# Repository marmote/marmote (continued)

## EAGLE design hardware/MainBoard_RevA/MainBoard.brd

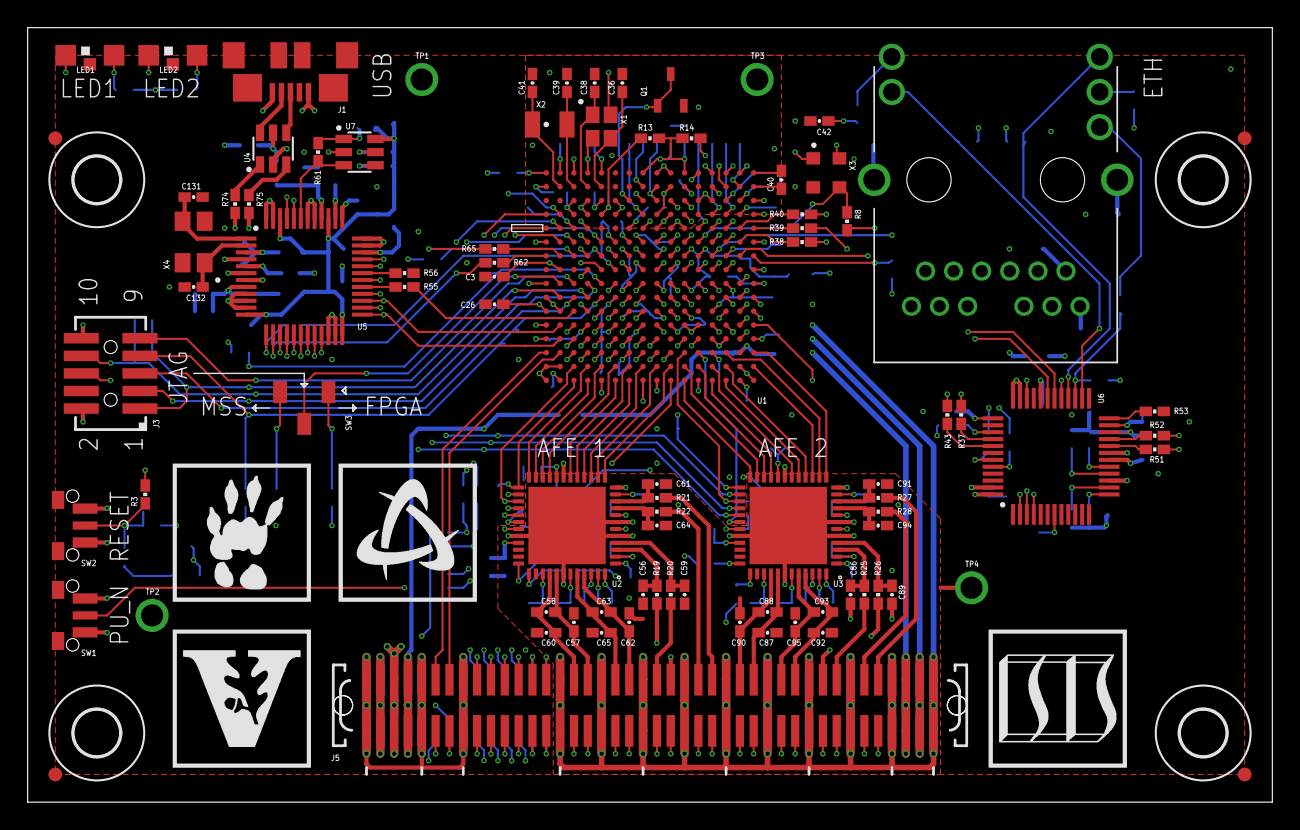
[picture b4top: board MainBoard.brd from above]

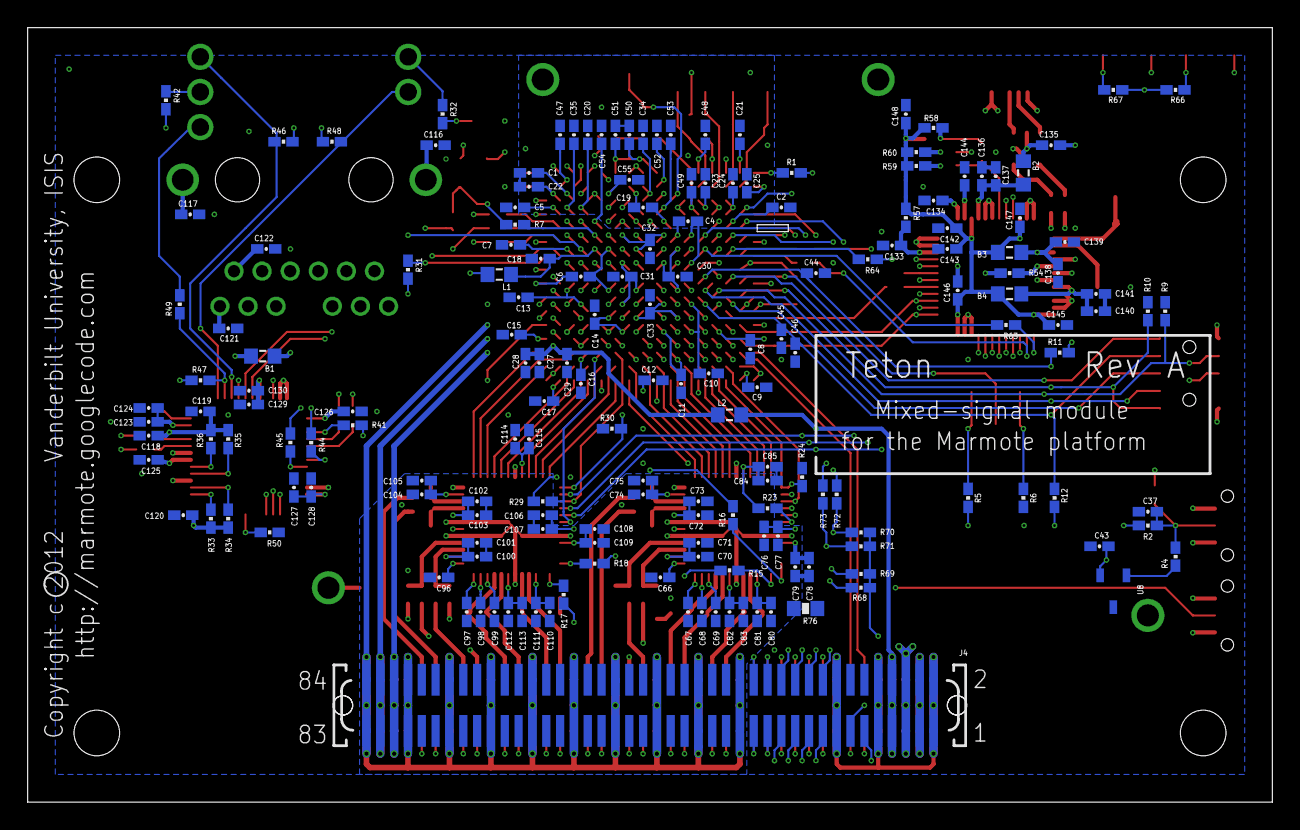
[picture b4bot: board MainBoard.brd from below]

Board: 6 copper layers, 90.0 x 56.0 mm, 269 parts (175 on the bottom side), 224 nets.

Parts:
B1: 70R/4A; L0603
B2, B3, B4: 600R/0.5A; L0603
C1, C40, C70, C72, C74, C76, C78, C80, C82, C84, C100, C102, C104, C106, C108, C110, C112, C114: 2.2uF; C0402
C2, C3, C4, C5, C6, C7, C8, C9, C10, C11, C12, C13, C14, C15, C16, C17, C18, C19, C20, C21, C22, C23, C24, C25, C26, C28, C30, C31, C32, C33, C34, C35, C37, C43, C44, C69, C71, C73, C75, C77, C79, C81, C83, C85, C99, C101, C103, C105, C107, C109, C111, C113, C115, C118, C119, C120, C121, C122, C124, C125, C126, C128, C130, C134, C137, C139, C141, C143, C144, C145, C146, C147, C148: 0.1uF; C0402
C27, C49, C50, C51, C123, C127, C129, C136, C138, C140, C142: 4.7uF; C0402
C29, C42, C46: 0.01uF; C0402
C36, C38, C131, C132: 10pF; C0402
C39, C41: 4pF; C0402
C45, C66, C67, C68, C96, C97, C98: 0.33uF; C0402
C47, C48, C52, C53, C54, C55, C57, C58, C60, C62, C63, C65, C87, C88, C90, C92, C93, C95: C0402
C56, C59, C61, C64, C86, C89, C91, C94: 22pF; C0402
C116, C117: 1000pF; C0402
C133, C135: 10nF; C0402
J1: CON-ZX62R-B-5P; ZX62R-B-5P
J2: CON-RJ45-J0G-0007NL; J0G-0007NL
J3: CON-FTSH-105-01-L-DV-K; FTSH-105-01-L-DV-K
J4: CON-71741-2184-BOT; 71742-3003-BOT
J5: CON-71741-2184-TOP; 71741-0002
L1, L2: 33nH; L0603
LED1, LED2: LED1208-RA
LOGO1: LOGO-VANDERBILT-600MIL-10MM-SS; LOGO-VANDERBILT-10MM-SILKSCREEN
LOGO2: LOGO-ISIS-600MIL-10MM-SS; LOGO-ISIS-10MM-SILKSCREEN
LOGO3: LOGO-MARMOTE-600MIL-10MM-SS; LOGO-MARMOTE-10MM-SILKSCREEN
LOGO4: LOGO-SMARTFUSION-600MIL-10MM-SS; LOGO-SMARTFUSION-10MM-SILKSCREEN
M1, M2, M3, M4: MOUNT-HOLE3.3; 3,3
M5, M6, M7, M8: FIDUCIAL1X2; FIDUCIAL-1X2
Q1: MMBT3904; SOT23-3L
R1, R2, R57, R58, R59, R60: 10k; R0402
R3, R7, R8, R62, R63, R64, R65: 39; R0402
R4, R11, R12, R13, R14, R15, R16, R17, R18, R49, R74, R75: 0; R0402
R5, R6, R9, R10: 1k; R0402
R19, R20, R21, R22, R25, R26, R27, R28: 24.9; R0402
R23, R24, R29, R30, R68, R69: 100k; R0402
R31: 1.5k; R0402
R32, R42, R66, R72, R73: 100; R0402
R33, R34, R35, R36: 49.9; R0402
R37, R38, R39, R40, R43, R44, R45: 22; R0402
R41, R46, R47, R48, R50, R51, R52: 2.2k; R0402
R53: 4.87k; R0402
R54: 12k; R0402
R55: 27; R0402
R56: 39k; R0402
R61: 2k; R0402
R67: 330; R0402
R70, R71: 4.7k; R0402
R76: 0; R0603
SW1, SW2: SWITCH-ESWITCH-TL3340G; TL3340
SW3: SWITCH-CJS-1200TA; SWITCH-DIP-CJS
TP1, TP2: TESTPOINT-YELLOW; TESTPOINT
TP3, TP4: TESTPOINT-GREEN; TESTPOINT
U1: A2F500M3G-1FGG256; FG256
U2, U3: MAX19706-T4877-4; TQFN-48
U4: USBLC6-2SC6; SOT23-6L
U5: FT232HL; LQFP-48
U6: DP83848C-VBH48A; LQFP-48
U7: 93LC56BT-OT; SOT23-6L
U8: DS1818-10-SOT-23; SOT23-3L
X1: ECX-2236-200; ECX-2236
X2: ECX-31B
X3: ASEM1-C; ASEM1
X4: ECX-42-120; ECX-42

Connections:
!AFE1_SHDN: R24.2, U1.A14, U2.25
!AFE2_SHDN: R30.2, U1.D6, U3.25
!MSS_RESET: R3.2, U1.K4, U6.29
!MSS_RESET_PB: C37.1, R2.1, R3.1, R4.2, SW2.2
!OE: U1.E16, U5.30
!PWRSAV: R56.1, U5.31
!RD: U1.D14, U5.26
!RXF: U1.D13, U5.21
!SIWU: U1.E14, U5.28
!SPI1_SS_AFE1: R23.1, U1.C14, U2.30
!SPI1_SS_AFE2: R29.1, U1.C5, U3.30
!TXE: U1.D15, U5.25
!USB_RESET: C133.1, R57.2, U5.34
!WAKEUP: J4.27, J5.27, R1.2, SW1.2, U1.T16
!WR: U1.E15, U5.27
A1V5: C34.1, C35.1, J4.79, J4.80, J5.79, J5.80, U1.N3, U1.P8, U1.R8
A3V3: C19.1, C20.1, C21.1, C22.1, C23.1, C24.1, C25.1, C69.1, C70.1, C71.1, C72.1, C73.1, C74.1, C75.1, C76.1, C77.1, C78.1, C79.1, C80.1, C81.1, C82.1, C83.1, C99.1, C100.1, C101.1, C102.1, C103.1, C104.1, C105.1, C106.1, C107.1, C108.1, C109.1, C110.1, C111.1, C112.1, C113.1, J4.81, J4.82, J5.81, J5.82, R14.2, U1.N4, U1.N8, U1.N14, U1.P2, U1.P12, U1.P14, U1.R7, U1.R16, U1.T15, U2.2, U2.8, U2.11, U2.31, U2.33, U2.39, U2.43, U2.46, U3.2, U3.8, U3.11, U3.31, U3.33, U3.39, U3.43, U3.46
ACBUS8: U1.E12, U5.32
ACBUS9: U1.F12, U5.33
ADC1+: J5.46, R19.2
ADC1-: J5.44, R20.2
ADC1-IAN: C59.2, R20.1, U2.4
ADC1-IAP: C56.1, R19.1, U2.3
ADC2+: J5.52, R21.2
ADC2-: J5.50, R22.2
ADC2-QAN: C64.2, R22.1, U2.9
ADC2-QAP: C61.1, R21.1, U2.10
ADC3+: J5.70, R25.2
ADC3-: J5.68, R26.2
ADC3-IAN: C89.2, R26.1, U3.4
ADC3-IAP: C86.1, R25.1, U3.3
ADC4+: J5.76, R27.2
ADC4-: J5.74, R28.2
ADC4-QAN: C94.2, R28.1, U3.9
ADC4-QAP: C91.1, R27.1, U3.10
AFE1_CLK: U1.A7, U2.6
AFE1_COM: C68.1, U2.47
AFE1_DB0: U1.B7, U2.13
AFE1_DB1: U1.B8, U2.14
AFE1_DB2: U1.B9, U2.15
AFE1_DB3: U1.A10, U2.16
AFE1_DB4: U1.B10, U2.17
AFE1_DB5: U1.A11, U2.18
AFE1_DB6: U1.B11, U2.21
AFE1_DB7: U1.B12, U2.22
AFE1_DB8: U1.A13, U2.23
AFE1_DB9: U1.B13, U2.24
AFE1_REFN: C67.1, U2.48
AFE1_REFP: C66.1, U2.1
AFE1_T/!R: U1.B14, U2.27
AFE2_CLK: U1.E1, U3.6
AFE2_COM: C98.1, U3.47
AFE2_DB0: U1.C1, U3.13
AFE2_DB1: U1.C3, U3.14
AFE2_DB2: U1.B1, U3.15
AFE2_DB3: U1.B3, U3.16
AFE2_DB4: U1.A3, U3.17
AFE2_DB5: U1.B4, U3.18
AFE2_DB6: U1.A4, U3.21
AFE2_DB7: U1.B5, U3.22
AFE2_DB8: U1.B6, U3.23
AFE2_DB9: U1.A6, U3.24
AFE2_REFN: C97.1, U3.48
AFE2_REFP: C96.1, U3.1
AFE2_T/!R: U1.C6, U3.27
AGND: C1.2, C19.2, C20.2, C21.2, C22.2, C23.2, C24.2, C25.2, C34.2, C35.2, C36.2, C38.2, C39.2, C41.2, C47.2, C48.2, C49.2, C50.2, C51.2, C52.2, C53.2, C54.2, C55.2, C56.2, C57.2, C59.1, C60.1, C61.2, C62.2, C64.1, C65.1, C66.2, C67.2, C68.2, C69.2, C70.2, C71.2, C72.2, C73.2, C74.2, C75.2, C76.2, C77.2, C78.2, C79.2, C80.2, C81.2, C82.2, C83.2, C86.2, C87.2, C89.1, C90.1, C91.2, C92.2, C94.1, C95.1, C96.2, C97.2, C98.2, C99.2, C100.2, C101.2, C102.2, C103.2, C104.2, C105.2, C106.2, C107.2, C108.2, C109.2, C110.2, C111.2, C112.2, C113.2, J4.29, J4.30, J4.35, J4.36, J4.41, J4.42, J4.47, J4.48, J4.53, J4.54, J4.59, J4.60, J4.65, J4.66, J4.71, J4.72, J4.77, J4.78, J4.83, J4.84, J5.29, J5.30, J5.35, J5.36, J5.41, J5.42, J5.47, J5.48, J5.53, J5.54, J5.59, J5.60, J5.65, J5.66, J5.71, J5.72, J5.77, J5.78, J5.83, J5.84, Q1.2, R76.2, TP3.1, TP4.1, U1.D2, U1.J4, U1.M6, U1.M7, U1.M8, U1.M10, U1.N7, U1.N11, U1.N13, U1.P1, U1.P4, U1.P5, U1.P11, U1.P13, U1.T4, U1.T7, U1.T8, U1.T13, U1.T14, U2.5, U2.7, U2.12, U2.32, U2.42, U2.EXP, U3.5, U3.7, U3.12, U3.32, U3.42, U3.EXP, X1.2, X1.4
ALERT: J4.25, J5.25, U1.J1
AUX_DAC1: R15.1, U2.37
AUX_DAC2: R16.1, U2.36
AUX_DAC3: R17.1, U3.37
AUX_DAC4: R18.1, U3.36
COM+: J2.16, R42.1
CRS: R37.2, U6.40
D1V5: C26.1, C30.1, C31.1, C32.1, C33.1, J4.7, J4.8, J5.7, J5.8, L2.2, U1.F8, U1.F10, U1.F16, U1.G7, U1.G9, U1.H8, U1.H10, U1.J7, U1.J9, U1.K8, U1.K10, U1.L7, U1.L9
D3V3: B1.1, C2.1, C3.1, C4.1, C5.1, C6.1, C7.1, C8.1, C9.1, C10.1, C11.1, C12.1, C13.1, C14.1, C15.1, C16.1, C17.1, C42.1, C43.1, C84.1, C85.1, C114.1, C115.1, C127.1, C128.1, C129.1, C130.1, J4.5, J4.6, J5.5, J5.6, L1.2, R1.1, R2.2, R5.2, R11.2, R12.2, R23.2, R29.2, R31.2, R32.2, R41.2, R42.2, R46.2, R47.2, R48.2, R66.2, R67.2, R68.2, R69.2, R70.2, R71.2, U1.A2, U1.A8, U1.A15, U1.C4, U1.C10, U1.D1, U1.D16, U1.E7, U1.E9, U1.E11, U1.E13, U1.F4, U1.F6, U1.G11, U1.H3, U1.H6, U1.J11, U1.J15, U1.K3, U1.K6, U1.L11, U1.M14, U1.N2, U2.20, U3.20, U6.32, U6.48, U8.2, X3.4
DAC1+: C57.1, C58.1, J5.34, U2.41
DAC1-: C58.2, C60.2, J5.32, U2.40
DAC2+: C62.1, C63.1, J5.40, U2.45
DAC2-: C63.2, C65.2, J5.38, U2.44
DAC3+: C87.1, C88.1, J5.58, U3.41
DAC3-: C88.2, C90.2, J5.56, U3.40
DAC4+: C92.1, C93.1, J5.64, U3.45
DAC4-: C93.2, C95.2, J5.62, U3.44
DGND: C2.2, C3.2, C4.2, C5.2, C6.2, C7.2, C8.2, C9.2, C10.2, C11.2, C12.2, C13.2, C14.2, C15.2, C16.2, C17.2, C18.2, C26.2, C27.2, C28.2, C29.2, C30.2, C31.2, C32.2, C33.2, C37.2, C42.2, C43.2, C44.2, C45.2, C46.2, C84.2, C85.2, C114.2, C115.2, C116.2, C117.2, C118.2, C119.2, C120.2, C121.2, C122.2, C123.2, C124.2, C125.2, C126.2, C127.2, C128.2, C129.2, C130.2, C131.2, C132.2, C133.2, C134.2, C135.2, C136.2, C137.2, C138.2, C139.2, C140.2, C141.2, C142.2, C143.2, C144.2, C145.2, C146.2, C147.2, C148.2, J1.5, J3.2, J3.10, J4.1, J4.2, J4.9, J4.10, J4.15, J4.16, J5.1, J5.2, J5.9, J5.10, J5.15, J5.16, R6.1, R9.1, R10.1, R24.1, R30.1, R50.1, R53.1, R54.1, R76.1, SW1.1, SW1.3, SW2.1, SW2.3, TP1.1, TP2.1, U1.A1, U1.A5, U1.A9, U1.A12, U1.A16, U1.B2, U1.B15, U1.B16, U1.C7, U1.C13, U1.D3, U1.D4, U1.D12, U1.E5, U1.E6, U1.E8, U1.E10, U1.F2, U1.F7, U1.F9, U1.F11, U1.F13, U1.F15, U1.G6, U1.G8, U1.G10, U1.G16, U1.H1, U1.H7, U1.H9, U1.H11, U1.H16, U1.J5, U1.J6, U1.J8, U1.J10, U1.K7, U1.K9, U1.K11, U1.K13, U1.L1, U1.L6, U1.L8, U1.L10, U1.L16, U1.M4, U1.N15, U2.19, U3.19, U4.2, U5.4, U5.9, U5.10, U5.11, U5.22, U5.23, U5.35, U5.36, U5.41, U5.42, U5.47, U5.48, U6.15, U6.19, U6.35, U6.36, U6.47, U7.2, U8.3, X3.2, X4.2, X4.4
E3V3: B1.2, C118.1, C119.1, C120.1, C121.1, C122.1, J2.6, J2.12, R33.2, R34.2, R35.2, R36.2, R51.2, R52.2, U6.22
EECLK: R59.1, U5.44, U7.4
EECS: R60.1, U5.45, U7.5
EEDATA: R61.2, U5.43, U7.3
EEDO: R58.1, R61.1, U7.1
ETH-RBIAS: R53.2, U6.24
EXTIC-RST: R4.1, U8.1
FPGATAP: R5.1, SW3.1
I2C0_SCL: J4.26, J5.26, R70.1, R72.2
I2C0_SCLI: R72.1, U1.J12
I2C0_SDA: J4.28, J5.28, R71.1, R73.2
I2C0_SDAI: R73.1, U1.J13
JTAGSEL: SW3.2, U1.H15
LED1: LED1.1, U1.H5
LED1H: LED1.2, R66.1
LED2: LED2.1, U1.H4
LED2H: LED2.2, R67.1
LED_ETH_ACT: J2.13, R48.1, U6.26
LED_ETH_LINK: J2.17, R46.1, U6.28
LED_ETH_SPD: J2.15, R49.2
LED_PHY_SPEED: R47.1, R49.1, U6.27
LPXIN: C39.1, U1.R14, X2.2
LPXOUT: C41.1, U1.R15, X2.1
MAC_CRS: R37.1, U1.L3
MAC_EN: R50.2, U1.J3, U6.7, X3.1
MAC_MDC: U1.K2, U6.31
MAC_MDIO: R31.1, U1.K1, U6.30
MAC_RMII_CLK: R7.2, U1.L5
MAC_RXD0: R44.1, U1.M3
MAC_RXD1: R45.1, U1.N1
MAC_RXER: R43.1, U1.L4
MAC_TXD0: R39.1, U1.M1
MAC_TXD1: R40.1, U1.M2
MAC_TXEN: R38.1, U1.L2
MAINXIN: C36.1, U1.R12, X1.3
MAINXOUT: C38.1, U1.R13, X1.1
MSSTAP: R6.2, SW3.3
NCAP: C40.2, U1.T1
NGPIO0: J5.11, U1.F3
NGPIO1: J5.13, U1.E3
NGPIO2: J5.17, U1.G3
NGPIO3: J5.19, U1.F1
PCAP: C40.1, U1.R1
PFBOUT: C123.1, C124.1, C125.1, C126.1, U6.18, U6.23, U6.37
PHY_RMII_CLK: R8.2, U6.34
RD+: J2.4, R34.1, U6.14
RD-: J2.5, R33.1, U6.13
REF_CLK+: J5.14, U1.C15
REF_CLK-: J5.12, U1.C16
RJ45-CHS-1: C116.1, J2.H$1
RJ45-CHS-2: C117.1, J2.H$2
RMII_CLK: R7.1, R8.1, X3.3
RSVD-P20: R51.1, U6.20
RSVD-P21: R52.1, U6.21
RXD_0/PHYAD1: R44.2, U6.43
RXD_1/PHYAD2: R45.2, U6.44
RX_DV: R41.1, U6.39
RX_ER: R43.2, U6.41
SF_ABPS0: J5.75, U1.R3
SF_ABPS1: J5.73, U1.T2
SF_ADC0: J5.49, U1.T5
SF_ADC1: C55.1, J5.51, R18.2, U1.R6
SF_ADC2: J5.55, U1.P7
SF_ADC3: C54.1, J5.57, R17.2, U1.M5
SF_ADC4: J5.45, U1.M9
SF_ADC5: C53.1, J5.43, R16.2, U1.N9
SF_ADC6: J5.39, U1.P9
SF_ADC7: C52.1, J5.37, R15.2, U1.R9
SF_CM0: J5.69, U1.T3
SF_CM1: J5.63, U1.P6
SF_DAC0: C47.1, J5.33, U1.R2
SF_DAC1: C48.1, J5.31, U1.T12
SF_TM0: J5.67, U1.R4
SF_TM1: J5.61, U1.N6
SF_TM3: Q1.1, Q1.3, U1.P10
SGPIO0: J4.11, U1.D5
SGPIO1: J4.13, U1.E4
SGPIO2: J4.17, U1.E2
SGPIO3: J4.19, U1.G1
SGPIO4: J4.21, U1.G2
SGPIO5: J4.23, U1.H2
SPI0_MISO: J4.22, U1.M16
SPI0_MOSI: J4.20, U1.N16
SPI0_SCLK: J4.18, U1.M15
SPI0_SS: J4.24, R68.1, U1.M13
SPI1_MISO: J5.22, U1.L15, U2.26, U3.26
SPI1_MOSI: J5.20, U1.L12, U2.28, U3.28
SPI1_SCLK: J5.18, U1.L14, U2.29, U3.29
SPI1_SS: J5.24, R69.1, U1.L13
TCK: J3.1, R10.2, U1.G15
TD+: J2.11, R36.1, U6.17
TD-: J2.10, R35.1, U6.16
TDI: J3.9, U1.H14
TDO: J3.3, U1.H13
TMS: J3.5, U1.G14
TRST: J3.8, R9.2, U1.G13
TXD_0: R39.2, U6.3
TXD_1: R40.2, U6.4
TX_EN: R38.2, U6.2
U3V3: B3.1, B4.1, C142.1, C143.1, C145.1, C146.1, C147.1, C148.1, R57.1, R58.2, R59.2, R60.2, U5.12, U5.24, U5.39, U5.46, U7.6
UART0_RXD: R63.2, U1.K12
UART0_TXD: R62.2, U1.K16
UART1_RXD: J5.23, R65.1
UART1_RXDI: R65.2, U1.K15
UART1_TXD: J5.21, R64.1
UART1_TXDI: R64.2, U1.K14
UREF: R54.2, U5.5
USBDM: R74.2, U5.6
USBDM-IN: J1.2, U4.6
USBDM-OUT: R74.1, U4.1
USBDP: R75.2, U5.7
USBDP-IN: J1.3, U4.4
USBDP-OUT: R75.1, U4.3
USB_CLK: R55.2, U1.F14
USB_CLKF: R55.1, U5.29
USB_DB0: R63.1, U1.C8, U5.13
USB_DB1: R62.1, U1.D8, U5.14
USB_DB2: U1.C9, U5.15
USB_DB3: U1.D9, U5.16
USB_DB4: U1.D10, U5.17
USB_DB5: U1.C11, U5.18
USB_DB6: U1.D11, U5.19
USB_DB7: U1.C12, U5.20
UXCSI: C131.1, U5.1, X4.3
UXCSO: C132.1, U5.2, X4.1
VAREFIN: C50.1, C51.1, R13.2, R14.1, U1.T6, U1.T9
VAREFOUT: C49.1, R13.1, U1.N12
VBUS: B2.1, C135.1, J1.1, U4.5
VCC3N: C1.1, U1.P3
VCCA: C134.1, U5.37
VCCPLL0: C27.1, C28.1, C29.1, L2.1, U1.C2
VCCRCOSC: C18.1, L1.1, U1.K5
VCORE: C144.1, U5.38
VJTAG: C44.1, J3.6, R11.1, U1.H12
VPHY: B3.2, C138.1, C139.1, U5.3
VPLL: B4.2, C140.1, C141.1, U5.8
VPUMP: C45.1, C46.1, J3.7, R12.1, U1.G12
VREGIN: B2.2, C136.1, C137.1, U5.40
VSUP: J4.3, J4.4, J5.3, J5.4
YEL+: J2.14, R32.1

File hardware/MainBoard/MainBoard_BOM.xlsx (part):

Bill of Materials for 'Marmote - Main Board (Rev A)'
Item # | Reference | Value | Package | Manufacturer | Manufacturer Part # | Supplier | Supplier Part # | Details | Qty | Unit Price | Total Cost
1 | B1 | 70R/4A | BEAD-BLM18SG700TN1D0603 | Murata | BLM18SG700TN1D | Digi-Key | 490-5224-1-ND | FERRITE CHIP 70 OHM 4000MA 0603 | 1 | 0.38 | 0.38
2 | B2, B3, B4 | 600R/0.5A | BEAD-BLM18EG601SN1D0603 | Murata | BLM18EG601SN1D | Digi-Key | 490-3994-2-ND | FILTER CHIP 600 OHM 500MA 0603 | 3 | 0.38 | 1.1400000000000001
3 | C1, C40, C70, C72, C74, C76, C78, C80, C82, C84, C100, C102, C104, C106, C108, 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 | 2.2uF | C0402 | Taiyo Yuden | LMK105BJ225MV-F | Digi-Key | 587-3153-1-ND | CAP CER 2.2UF 10V 20% X5R 0402 | 18 | 0.3 | 5.3999999999999995
4 | C2, C3, C4, C5, C6, C7, C8, C9, C10, C11, C12, C13, C14, C15, C16, C17, C18, C1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 | 0.1uF | C0402 | TDK | C1005X7R1C104K | Digi-Key | 445-4952-1-ND | CAP CER 0.1UF 16V 10% X7R 0402 | 73 | 0.09 | 6.5699999999999994
5 | C29, C42, C46, C133, C135 | 0.01uF | C0402 | TDK | C1005X7R1C103M | Digi-Key | 445-4943-1-ND | CAP CER 10000PF 16V 20% X7R 0402 | 5 | 0.08 | 0.4
6 | C36, C38, C131, C132 | 10pF | C0402 | TDK | C1005C0G1H100D | Digi-Key | 445-1235-1-ND | CAP CER 10PF 50V NP0 0402 | 4 | 0.08 | 0.32
7 | C39, C41 | 4pF | C0402 | TDK | CGA2B2C0G1H040C | Digi-Key | 445-5576-1-ND | CAP CER 4PF 50V NP0 0402 | 2 | 0.2 | 0.4
8 | C45, C66, C67, C68, C96, C97, C98 | 0.33uF | C0402 | TDK | C1005X5R1C334K | Digi-Key | 445-4974-1-ND | CAP CER 0.33UF 16V 10% X5R 0402 | 7 | 0.28000000000000003 | 1.9600000000000002
9 | C47, C48, C52, C53, C54, C55, C57, C58, C60, C62, C63, C65, C87, C88, C90, C92,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 | DNP | C0402 |  |  |  |  | CAPACITOR | 18 |  | 0
10 | C56, C59, C61, C64, C86, C89, C91, C94 | 22pF | C0402 | TDK | C1005C0G1H220J | Digi-Key | 445-1239-1-ND | CAP CER 22PF 50V 5% NP0 0402 | 8 | 0.08 | 0.64
11 | C116, C117 | 1000pF | C0402 | TDK | C1005X7R1C102K | Digi-Key | 445-6848-1-ND | CAP CER 1000PF 16V 10% X7R 0402 | 2 | 0.08 | 0.16
12 | C27, C49, C50, C51, C123, C127, C129, C136, C138, C140, C142 | 4.7uF | C0402 | TDK | C1005X5R1A475M | Digi-Key | 445-8023-1-ND | CAP CER 4.7UF 10V 20% X5R 0402 | 11 | 0.53 | 5.83
13 | J1 | CON-ZX62R-B-5P | CON-ZX62R-B-5P | Hirose | ZX62R-B-5P | Digi-Key | H11574CT-ND | ZX62R-B-5P | 1 | 1.6 | 1.6
14 | J2 | CON-RJ45-J0G-0007NL | CON-RJ45-J0G-0007NL | Pulse Electronics Corporation | J0G-0007NL | Digi-Key | 553-1662-ND | RJ45 connector | 1 | 8.2100000000000009 | 8.2100000000000009
15 | J3 | CON-FTSH-105-01-L-DV-K | CON-FTSH-105-01-L-DV-K | Samtec | FTSH-105-01-L-DV-K | Digi-Key | FTSH-105-01-L-DV-K-ND | CONN HEADER 10 POS DUAL .05" SMD | 1 | 3.45 | 3.45
16 | J4 | CON-71741-2184-BOT | CON-71741-2184-BOT | Molex | 71742-3003 | Digi-Key | WM3499CT-ND | MEZZANINE 1MM BTB RECPT 84CKT | 1 | 5.81 | 5.81
17 | J5 | CON-71741-2184-TOP | CON-71741-2184-TOP | Molex | 71741-0002 | Digi-Key | WM3498CT-ND | MEZZANINE 1MM BTB PLUG 84CKT | 1 | 6.24 | 6.24
18 | L1, L2 | 33nH | L0603 | JW Miller | PM0603-33NJ-RC | Digi-Key | M8487CT-ND | INDUCTOR CHIP 33NH 5% SMD | 2 |  | 0
19 | LED1 | LED-MGC-3010 | LED-MGC-3010 | Kingbright | APECVA3010MGC | Digi-Key | 754-1364-1-ND | LED 3.0X1.0MM 568NM GRN RA SMD | 1 | 0.6 | 0.6
20 | LED2 | LED-ECK-3010 | LED-ECK-3010 | Kingbright | APECVA3010SECK | Digi-Key | 754-1367-1-ND | LED 3X1MM 601NM ORN RA CHIP SMD | 1 | 0.33 | 0.33
21 | Q1 | MMBT3904 | MMBT3904 | Fairchild Semiconductor | MMBT3904 | Digi-Key | MMBT3904FSCT-ND | TRANSISTOR GP NPN AMP SOT-23 | 1 | 0.37 | 0.37
22 | R1, R2, R57, R58, R59, R60 | 10k | R0402 | Rohm | MCR01MRTF1002 | Digi-Key | RHM10.0KCDCT-ND | RES 10.0K OHM 1/16W 1% 0402 SMD | 6 | 2.3E-2 | 0.13800000000000001
23 | R19, R20, R21, R22, R25, R26, R27, R28 | 24.9 | R0402 | Vishay Dale | CRCW040224R9FKED | Digi-Key | 541-24.9LCT-ND | RES 24.9 OHM 1/16W 1% 0402 SMD | 8 | 8.3000000000000004E-2 | 0.66400000000000003
24 | R23, R24, R29, R30, R68, R69 | 100k | R0402 | Rohm | TRR01MZPF1003 | Digi-Key | RHM100KBHCT-ND | RES 100K OHM 1/16W 1% 0402 SMD | 6 | 0.123 | 0.73799999999999999
25 | R3, R7, R8, R62, R63, R64, R65 | 39 | R0402 | Rohm | MCR01MZPF39R0 | Digi-Key | RHM39.0LCT-ND | RES 39.0 OHM 1/16W 1% 0402 SMD | 7 | 2.5999999999999999E-2 | 0.182
26 | R31 | 1.5k | R0402 | Rohm | TRR01MZPF1501 | Digi-Key | RHM1.50KBHCT-ND | RES 1.50K OHM 1/16W 1% 0402 SMD | 1 | 0.123 | 0.123
27 | R32, R42 | 100 | R0402 | Rohm | TRR01MZPF1000 | Digi-Key | RHM100BHCT-ND | RES 100 OHM 1/16W 1% 0402 SMD | 2 | 0.20100000000000001 | 0.40200000000000002
28 | R33, R34, R35, R36 | 49.9 | R0402 | Rohm | MCR01MRTF49R9 | Digi-Key | RHM49.9CDCT-ND | RES 49.9 OHM 1/16W 1% 0402 SMD | 4 | 2.3E-2 | 9.1999999999999998E-2
29 | R37, R38, R39, R40, R43, R44, R45 | 22 | R0402 | Rohm | MCR01MRTF22R0 | Digi-Key | RHM22.0CDCT-ND | RES 22.0 OHM 1/16W 1% 0402 SMD | 7 | 2.3E-2 | 0.161
30 | R4, R11, R12, R13, R14, R15, R16, R17, R18, R49, R74, R75 | 0 | R0402 | Rohm | TRR01MZPJ000 | Digi-Key | RHM0.0BICT-ND | RES 0.0 OHM 1/16W 0402 SMD | 12 | 0.18099999999999999 | 2.1719999999999997
31 | R41, R46, R47, R48, R50, R51, R52 | 2.2k | R0402 | Rohm | MCR01MRTF2201 | Digi-Key | RHM2.20KCDCT-ND | RES 2.20K OHM 1/16W 1% 0402 SMD | 7 | 2.3E-2 | 0.161
32 | R5, R6, R9, R10 | 1k | R0402 | Rohm | TRR01MZPF1001 | Digi-Key | RHM1.00KBHCT-ND | RES 1.00K OHM 1/16W 1% 0402 SMD | 4 | 0.123 | 0.49199999999999999
33 | R53 | 4.87k | R0402 | Vishay Dale | CRCW04024R87FKED | Digi-Key | 541-4.87LLCT-ND | RES 4.87 OHM 1/16W 1% 0402 SMD | 1 | 8.3000000000000004E-2 | 8.3000000000000004E-2
34 | R54 | 12k | R0402 | Vishay Dale | CRCW040212K0FKED | Digi-Key | 541-12.0KLCT-ND | RES 12.0K OHM 1/16W 1% 0402 SMD | 1 | 8.3000000000000004E-2 | 8.3000000000000004E-2
35 | R55 | 27 | R0402 | Vishay Dale | CRCW040227R0FKED | Digi-Key | 541-27.0LCT-ND | RES 27.0 OHM 1/16W 1% 0402 SMD | 1 | 8.3000000000000004E-2 | 8.3000000000000004E-2
36 | R56 | 39k | R0402 | Vishay Dale | CRCW040239K0FKED | Digi-Key | 541-39.0KLCT-ND | RES 39.0K OHM 1/16W 1% 0402 SMD | 1 | 8.3000000000000004E-2 | 8.3000000000000004E-2
37 | R61 | 2k | R0402 | Vishay Dale | CRCW04022K00FKED | Digi-Key | 541-2.00KLCT-ND | RES 2.00K OHM 1/16W 1% 0402 SMD | 1 | 8.3000000000000004E-2 | 8.3000000000000004E-2
38 | R66, R72, R73 | 100 | R0402 | Vishay Dale | CRCW0402100RFKED | Digi-Key | 541-100LCT-ND | RES 100 OHM 1/16W 1% 0402 SMD | 3 | 8.3000000000000004E-2 | 0.249
39 | R67 | 330 | R0402 | Vishay Dale | CRCW0402330RFKED | Digi-Key | 541-330LCT-ND | RES 330 OHM 1/16W 1% 0402 SMD | 1 | 8.3000000000000004E-2 | 8.3000000000000004E-2
40 | R70, R71 | 4.7k | R0402 | Vishay Dale | CRCW04024K70FKED | Digi-Key | 541-4.70KLCT-ND | RES 4.70K OHM 1/16W 1% 0402 SMD | 2 | 8.3000000000000004E-2 | 0.16600000000000001
41 | R76 | DNP | R0603 |  |  |  |  | RESISTOR | 1 |  | 0
42 | SW1, SW2 | SWITCH-ESWITCH-TL3340G | SWITCH-ESWITCH-TL3340G | E-Switch | TL3340AF160QG | Digi-Key | EG4627CT-ND | SWITCH TACTILE SPST-NO 0.05A 12V | 2 | 0.29099999999999998 | 0.58199999999999996
43 | SW3 | SWITCH-CJS-1200-1200 | J-Lead | CJS | CJS-1200TA | Digi-Key | 563-1021-1-ND | CJS-1200 SPDT Switch | 1 | 0.97 | 0.97
44 | TP1, TP2 | TESTPOINT-YELLOW | TESTPOINT-YELLOW | Keystone | 5009 | Digi-Key | 5009K-ND | TEST POINT PC COMPACT .063"D YLW | 2 | 0.35 | 0.7
45 | TP3, TP4 | TESTPOINT-GREEN | TESTPOINT-GREEN | Keystone | 5121 | Digi-Key | 5121K-ND | TEST POINT PC COMPACT T/H GREEN | 2 | 0.35 | 0.7
46 | U1 | A2F500M3G-1FGG256 | A2F500M3G-1FGG256 | Microsemi | A2F500M3G-1FGG256 | Digi-Key | 1100-1007-ND | IC FPGA 512K FLASH 256FPBGA | 1 | 53.91 | 53.91
47 | U2, U3 | MAX19706-T4877-4 | MAX19706-T4877-4 | Maxim | MAX19706ETM+ | Digi-Key | MAX19706ETM+-ND | IC ANLG FRNT END 48-TQFN | 2 | 20.09 | 40.18
48 | U4 | USBLC6-2SC6 | USBLC6-2SC6 | STMicroelectronics | USBLC6-2SC6 | Digi-Key | 497-5235-1-ND | USBLC6-2SC6 | 1 | 0.95 | 0.95
49 | U5 | FT232HL | FT232HL | FTDI | 768-1101-1-ND | Digi-Key | 768-1101-1-ND | IC HS USB TO UART/FIFO 48LQFP | 1 | 4.25 | 4.25
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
